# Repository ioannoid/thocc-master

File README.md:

the repo name is a funny, please don't hate

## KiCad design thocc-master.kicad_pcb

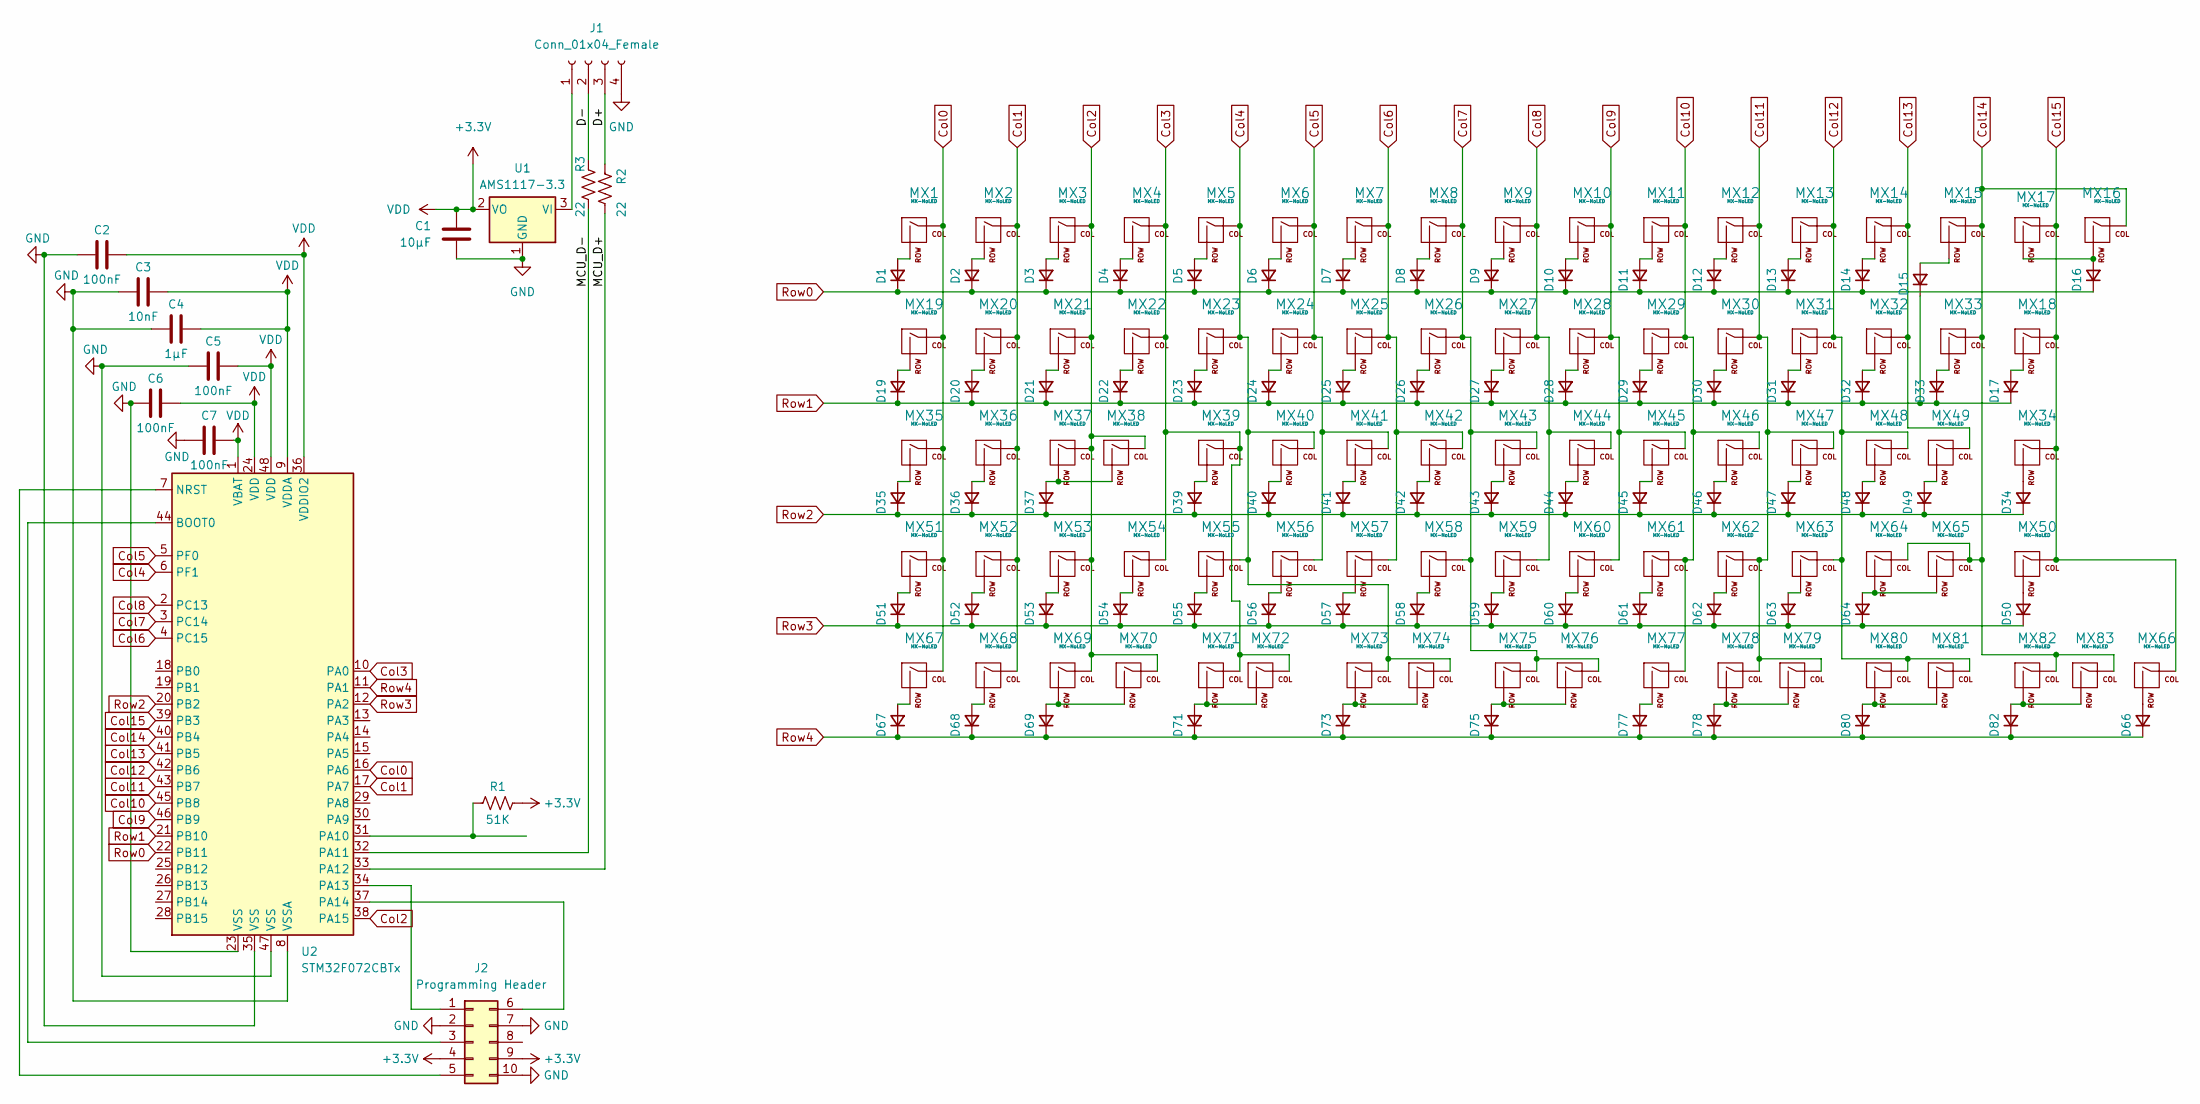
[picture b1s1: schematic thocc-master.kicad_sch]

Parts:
C1: 10μF; C_0805_2012Metric
C2, C5, C6, C7: 100nF; C_0805_2012Metric
C3: 10nF; C_0805_2012Metric
C4: 1μF; C_0805_2012Metric
D1, D2, D3, D4, D5, D6, D7, D8, D9, D10, D11, D12, D13, D14, D15, D16, D17, D19, D20, D21, D22, D23, D24, D25, D26, D27, D28, D29, D30, D31, D32, D33, D34, D35, D36, D37, D39, D40, D41, D42, D43, D44, D45, D46, D47, D48, D49, D50, D51, D52, D53, D54, D55, D56, D57, D58, D59, D60, D61, D62, D63, D64, D66, D67, D68, D69, D71, D73, D75, D77, D78, D80, D82: D_Small; D_SOD-123
J1: Conn_01x04_Female; JST_SH_SM04B-SRSS-TB_1x04-1MP_P1.00mm_Horizontal
J2: Programming Header; PinSocket_2x05_P2.00mm_Vertical
MX1, MX2, MX3, MX4, MX5, MX6, MX7, MX8, MX9, MX10, MX11, MX12, MX13, MX14, MX15, MX16, MX18, MX19, MX20, MX21, MX22, MX23, MX24, MX25, MX26, MX27, MX28, MX29, MX30, MX31, MX32, MX33, MX34, MX35, MX36, MX37, MX38, MX39, MX40, MX41, MX42, MX43, MX44, MX45, MX46, MX47, MX48, MX49, MX51, MX52, MX54, MX55, MX56, MX57, MX58, MX59, MX60, MX61, MX62, MX63, MX64, MX66, MX67, MX68, MX69, MX70, MX71, MX72, MX73, MX74, MX77, MX78, MX79, MX80, MX81, MX82, MX83: MX-NoLED; MXOnly-1U-NoLED
MX17, MX50, MX53, MX65: MX-NoLED; MXOnly-2U-NoLED
MX75: MX-NoLED; MXOnly-6.25U-ReversedStabilizers-NoLED
MX76: MX-NoLED; MXOnly-7U-ReversedStabilizers-NoLED
R1: 51K; R_0805_2012Metric
R2, R3: 22; R_0805_2012Metric
U1: AMS1117-3.3; SOT-223-3_TabPin2
U2: STM32F072CBTx; LQFP-48_7x7mm_P0.5mm

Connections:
+3.3V: C1.1, C2.2, C3.2, C4.2, C5.2, C6.2, C7.2, J2.4, J2.9, R1.2, U1.2 (VO), U2.1 (VBAT), U2.9 (VDDA), U2.24 (VDD), U2.36 (VDDIO2), U2.48 (VDD)
/D+: J1.3, R2.1
/D-: J1.2, R3.1
/MCU_D+: R2.2, U2.33 (PA12)
/MCU_D-: R3.2, U2.32 (PA11)
Col0: MX1.1 (COL), MX19.1 (COL), MX35.1 (COL), MX51.1 (COL), MX67.1 (COL), U2.16 (PA6)
Col1: MX2.1 (COL), MX20.1 (COL), MX36.1 (COL), MX52.1 (COL), MX68.1 (COL), U2.17 (PA7)
Col2: MX3.1 (COL), MX21.1 (COL), MX37.1 (COL), MX38.1 (COL), MX53.1 (COL), MX69.1 (COL), MX70.1 (COL), U2.38 (PA15)
Col3: MX4.1 (COL), MX22.1 (COL), MX39.1 (COL), MX54.1 (COL), MX71.1 (COL), MX72.1 (COL), U2.10 (PA0)
Col4: MX5.1 (COL), MX23.1 (COL), MX40.1 (COL), MX55.1 (COL), MX73.1 (COL), MX74.1 (COL), U2.6 (PF1)
Col5: MX6.1 (COL), MX24.1 (COL), MX41.1 (COL), MX56.1 (COL), U2.5 (PF0)
Col6: MX7.1 (COL), MX25.1 (COL), MX42.1 (COL), MX57.1 (COL), U2.4 (PC15)
Col7: MX8.1 (COL), MX26.1 (COL), MX43.1 (COL), MX58.1 (COL), MX75.1 (COL), MX76.1 (COL), U2.3 (PC14)
Col8: MX9.1 (COL), MX27.1 (COL), MX44.1 (COL), MX59.1 (COL), U2.2 (PC13)
Col9: MX10.1 (COL), MX28.1 (COL), MX45.1 (COL), MX60.1 (COL), U2.46 (PB9)
Col10: MX11.1 (COL), MX29.1 (COL), MX46.1 (COL), MX61.1 (COL), MX77.1 (COL), U2.45 (PB8)
Col11: MX12.1 (COL), MX30.1 (COL), MX47.1 (COL), MX62.1 (COL), MX78.1 (COL), MX79.1 (COL), U2.43 (PB7)
Col12: MX13.1 (COL), MX31.1 (COL), MX48.1 (COL), MX63.1 (COL), MX80.1 (COL), MX81.1 (COL), U2.42 (PB6)
Col13: MX14.1 (COL), MX32.1 (COL), MX49.1 (COL), U2.41 (PB5)
Col14: MX15.1 (COL), MX16.1 (COL), MX33.1 (COL), MX64.1 (COL), MX65.1 (COL), MX82.1 (COL), MX83.1 (COL), U2.40 (PB4)
Col15: MX17.1 (COL), MX18.1 (COL), MX34.1 (COL), MX50.1 (COL), MX66.1 (COL), U2.39 (PB3)
GND: C1.2, C2.1, C3.1, C4.1, C5.1, C6.1, C7.1, J1.4, J2.2, J2.7, J2.10, U1.1 (GND), U2.8 (VSSA), U2.23 (VSS), U2.35 (VSS), U2.47 (VSS)
unnamed: D1.2 (A), MX1.2 (ROW)
unnamed: D2.2 (A), MX2.2 (ROW)
unnamed: D3.2 (A), MX3.2 (ROW)
unnamed: D4.2 (A), MX4.2 (ROW)
unnamed: D5.2 (A), MX5.2 (ROW)
unnamed: D6.2 (A), MX6.2 (ROW)
unnamed: D7.2 (A), MX7.2 (ROW)
unnamed: D8.2 (A), MX8.2 (ROW)
unnamed: D9.2 (A), MX9.2 (ROW)
unnamed: D10.2 (A), MX10.2 (ROW)
unnamed: D11.2 (A), MX11.2 (ROW)
unnamed: D12.2 (A), MX12.2 (ROW)
unnamed: D13.2 (A), MX13.2 (ROW)
unnamed: D14.2 (A), MX14.2 (ROW)
unnamed: D15.2 (A), MX15.2 (ROW)
unnamed: D16.2 (A), MX16.2 (ROW), MX17.2 (ROW)
unnamed: D17.2 (A), MX18.2 (ROW)
unnamed: D19.2 (A), MX19.2 (ROW)
unnamed: D20.2 (A), MX20.2 (ROW)
unnamed: D21.2 (A), MX21.2 (ROW)
unnamed: D22.2 (A), MX22.2 (ROW)
unnamed: D23.2 (A), MX23.2 (ROW)
unnamed: D24.2 (A), MX24.2 (ROW)
unnamed: D25.2 (A), MX25.2 (ROW)
unnamed: D26.2 (A), MX26.2 (ROW)
unnamed: D27.2 (A), MX27.2 (ROW)
unnamed: D28.2 (A), MX28.2 (ROW)
unnamed: D29.2 (A), MX29.2 (ROW)
unnamed: D30.2 (A), MX30.2 (ROW)
unnamed: D31.2 (A), MX31.2 (ROW)
unnamed: D32.2 (A), MX32.2 (ROW)
unnamed: D33.2 (A), MX33.2 (ROW)
unnamed: D34.2 (A), MX34.2 (ROW)
unnamed: D35.2 (A), MX35.2 (ROW)
unnamed: D36.2 (A), MX36.2 (ROW)
unnamed: D37.2 (A), MX37.2 (ROW), MX38.2 (ROW)
unnamed: D39.2 (A), MX39.2 (ROW)
unnamed: D40.2 (A), MX40.2 (ROW)
unnamed: D41.2 (A), MX41.2 (ROW)
unnamed: D42.2 (A), MX42.2 (ROW)
unnamed: D43.2 (A), MX43.2 (ROW)
unnamed: D44.2 (A), MX44.2 (ROW)
unnamed: D45.2 (A), MX45.2 (ROW)
unnamed: D46.2 (A), MX46.2 (ROW)
unnamed: D47.2 (A), MX47.2 (ROW)
unnamed: D48.2 (A), MX48.2 (ROW)
unnamed: D49.2 (A), MX49.2 (ROW)
unnamed: D50.2 (A), MX50.2 (ROW)
unnamed: D51.2 (A), MX51.2 (ROW)
unnamed: D52.2 (A), MX52.2 (ROW)
unnamed: D53.2 (A), MX53.2 (ROW)
unnamed: D54.2 (A), MX54.2 (ROW)
unnamed: D55.2 (A), MX55.2 (ROW)
unnamed: D56.2 (A), MX56.2 (ROW)
unnamed: D57.2 (A), MX57.2 (ROW)
unnamed: D58.2 (A), MX58.2 (ROW)
unnamed: D59.2 (A), MX59.2 (ROW)
unnamed: D60.2 (A), MX60.2 (ROW)
unnamed: D61.2 (A), MX61.2 (ROW)
unnamed: D62.2 (A), MX62.2 (ROW)
unnamed: D63.2 (A), MX63.2 (ROW)
unnamed: D64.2 (A), MX64.2 (ROW), MX65.2 (ROW)
unnamed: D66.2 (A), MX66.2 (ROW)
unnamed: D67.2 (A), MX67.2 (ROW)
unnamed: D68.2 (A), MX68.2 (ROW)
unnamed: D69.2 (A), MX69.2 (ROW), MX70.2 (ROW)
unnamed: D71.2 (A), MX71.2 (ROW), MX72.2 (ROW)
unnamed: D73.2 (A), MX73.2 (ROW), MX74.2 (ROW)
unnamed: D75.2 (A), MX75.2 (ROW), MX76.2 (ROW)
unnamed: D77.2 (A), MX77.2 (ROW)
unnamed: D78.2 (A), MX78.2 (ROW), MX79.2 (ROW)
unnamed: D80.2 (A), MX80.2 (ROW), MX81.2 (ROW)
unnamed: D82.2 (A), MX82.2 (ROW), MX83.2 (ROW)
unnamed: J1.1, U1.3 (VI)
unnamed: J2.1, U2.34 (PA13)
unnamed: J2.3, U2.44 (BOOT0)
unnamed: J2.5, U2.7 (NRST)
unnamed: J2.6, U2.37 (PA14)
unnamed: R1.1, U2.31 (PA10)
Row0: D1.1 (K), D2.1 (K), D3.1 (K), D4.1 (K), D5.1 (K), D6.1 (K), D7.1 (K), D8.1 (K), D9.1 (K), D10.1 (K), D11.1 (K), D12.1 (K), D13.1 (K), D14.1 (K), D16.1 (K), U2.22 (PB11)
Row1: D15.1 (K), D17.1 (K), D19.1 (K), D20.1 (K), D21.1 (K), D22.1 (K), D23.1 (K), D24.1 (K), D25.1 (K), D26.1 (K), D27.1 (K), D28.1 (K), D29.1 (K), D30.1 (K), D31.1 (K), D32.1 (K), D33.1 (K), U2.21 (PB10)
Row2: D34.1 (K), D35.1 (K), D36.1 (K), D37.1 (K), D39.1 (K), D40.1 (K), D41.1 (K), D42.1 (K), D43.1 (K), D44.1 (K), D45.1 (K), D46.1 (K), D47.1 (K), D48.1 (K), D49.1 (K), U2.20 (PB2)
Row3: D50.1 (K), D51.1 (K), D52.1 (K), D53.1 (K), D54.1 (K), D55.1 (K), D56.1 (K), D57.1 (K), D58.1 (K), D59.1 (K), D60.1 (K), D61.1 (K), D62.1 (K), D63.1 (K), D64.1 (K), U2.12 (PA2)
Row4: D66.1 (K), D67.1 (K), D68.1 (K), D69.1 (K), D71.1 (K), D73.1 (K), D75.1 (K), D77.1 (K), D78.1 (K), D80.1 (K), D82.1 (K), U2.11 (PA1)

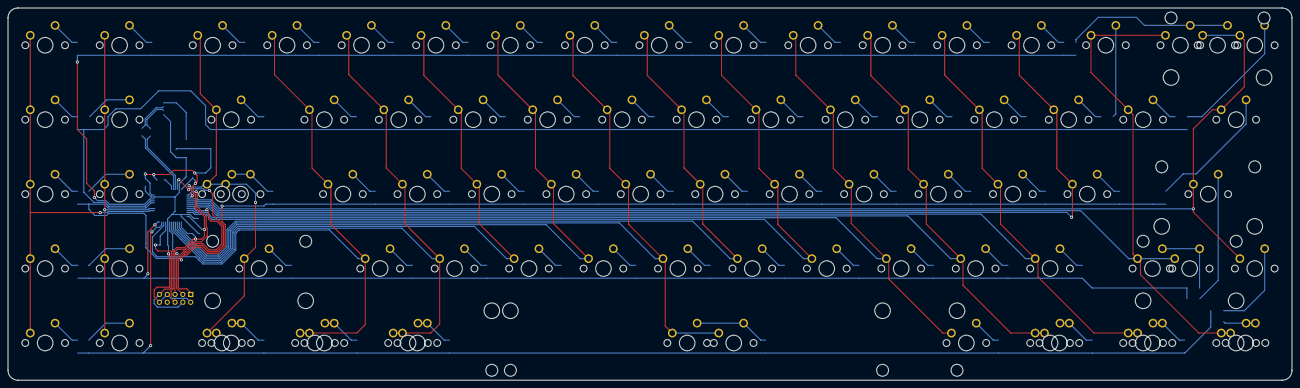
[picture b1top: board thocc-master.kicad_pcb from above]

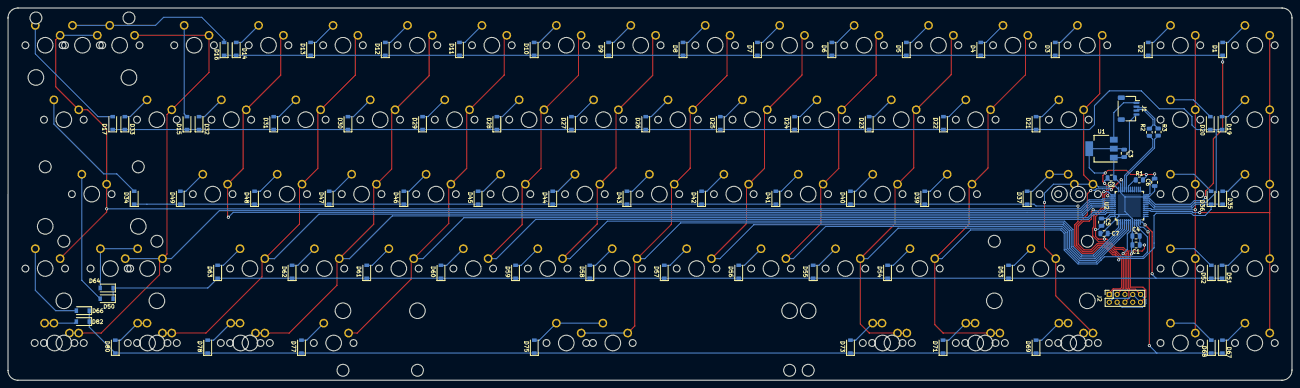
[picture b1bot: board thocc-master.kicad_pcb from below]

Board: 2 copper layers, 328.6 x 95.3 mm, 170 parts (87 on the bottom side), 106 nets.

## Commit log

2022-08-26 Finished PCB
2022-08-26 The actual keyboard is called voyager
2022-08-26 Removed gerber
2022-08-26 i hope this isn't a disaster
